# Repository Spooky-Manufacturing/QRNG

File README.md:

# QRNG
Quantum Random Number Generator

# Motivation
The QRNGv1 (Now QRNG_BASIC) was originally a proof of concept for quantum technology applications, specifically in this case for the generation of entropy which has a broad range of uses from generating graphics to encryption keys.

# How It Works
The device uses a polarizing beam splitter to split a laser pulse into two beams with a 50/50 probability of a photon in the beam traveling either path. The photons actually travel as a wave, meaning they both pass through and are reflected by the beam splitter. This creates what's known as the superposition of light where the light remains in both paths able to interfere with itself until it is measured and collapses out of superposition.

The equivalent quantum logic gate would be the Hadamard gate, in QASM code:

```qasm
creg c0[1];
h q[1];
measure q[1] -> c0;
```

# Hardware Requirements
- Arduino Uno (or similar)
- Breadboard
- 2x Photoresistors
- 1x 50/50 Polarizing beam splitter
- 1x Laser Diode

# Software Requirements
- Arduino IDE (for programming the Arduino)

# Firmware
Firmware can be found in the respective design folders labelled according to version. The schematics as well are labelled with the version of firmware which supports them.

# How To Use
Currently the QRNG arduino operates via the Arduino Serial Monitor, you can issue single letter commands to it. We plan to add support for the device with our [Qubit Controller](https://github.com/Spooky-Manufacturing/Qubit-Controller) in the near future.

## Available Commands
- v : Version, returns the current firmware verison
- t : Test command, should return 'Success!' on the monitor
- e : Enables extraneous information
- r : Returns a random bit generated by the RNG
- h : Produces a hadamard operation on the qubit, returning the measured angle of the qubit

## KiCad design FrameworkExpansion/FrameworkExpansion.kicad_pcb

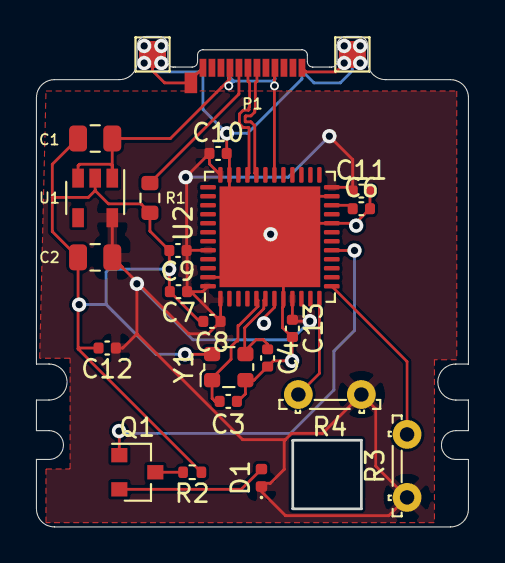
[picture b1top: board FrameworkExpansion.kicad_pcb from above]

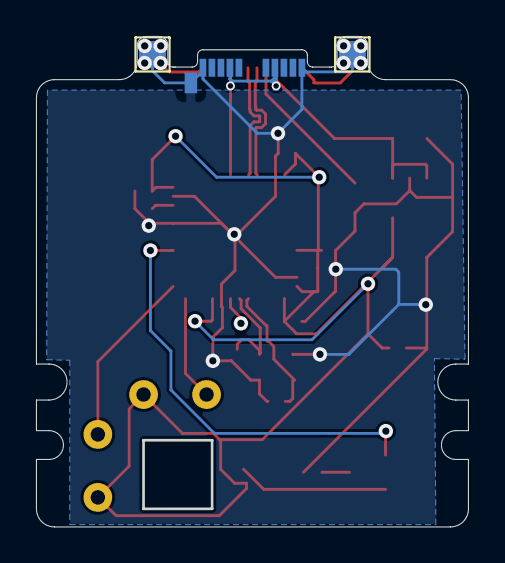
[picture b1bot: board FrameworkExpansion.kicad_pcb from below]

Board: 2 copper layers, 23.9 x 27.2 mm, 26 parts (2 on the bottom side), 14 nets.

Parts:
C1, C2: 10uF; C_0805_2012Metric
C3, C4: C_Small; C_0402_1005Metric
C6: 4.7uF; C_0402_1005Metric
C7, C8, C9, C10, C11, C12, C13: 100nF; C_0402_1005Metric
D1: LED; LED_0402_1005Metric
P1: USB_C_Plug_USB2.0; USB_C_Plug_Molex_105444
Q1: Q_NPN_BCE; SOT-23
R1: 5.1k; R_0603_1608Metric
R2: 10k; R_0402_1005Metric
R3, R4: R_PHOTO; R_LDR_5.2x5.2mm_P3.5mm_Horizontal
TP1, TP2, TP3, TP4: TestPoint; TestPoint_Pad_1.5x1.5mm
U1: AP2112K-3.3; SOT-23-5
U2: STM32F411CEUx; QFN-48-1EP_7x7mm_P0.5mm_EP5.6x5.6mm
Y1: Crystal_GND24; Oscillator_SMD_ECS_2520MV-xxx-xx-4Pin_2.5x2.0mm

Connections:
+3V3: C2.1, C7.1, C8.1, C9.1, C10.1, C11.1, C12.1, C13.1, D1.1, R3.1, R4.1, U1.5, U2.1, U2.9, U2.24, U2.36, U2.44, U2.48
/HORIZONTAL: R4.2, U2.12
/TRIGGER: Q1.1, U2.17
/USB_DN: P1.A7, U2.32
/USB_DP: P1.A6, U2.33
/VERTICAL: R3.2, U2.13
/XTAL_N: C4.1, U2.6, Y1.3
/XTAL_P: C3.1, U2.5, Y1.1
GND: C1.2, C2.2, C3.2, C4.2, C6.2, C7.2, C8.2, C9.2, C10.2, C11.2, C12.2, C13.2, P1.A1, P1.A12, P1.B1, P1.B12, P1.S1, R1.2, R2.1, TP1.1, TP2.1, TP3.1, TP4.1, U1.2, U2.8, U2.20, U2.23, U2.35, U2.47, U2.49, Y1.2, Y1.4
unnamed: C6.1, U2.22
unnamed: D1.2, Q1.2
unnamed: P1.A5, R1.1
unnamed: Q1.3, R2.2
VBUS: C1.1, P1.A4, P1.A9, P1.B4, P1.B9, U1.1, U1.3, U2.30

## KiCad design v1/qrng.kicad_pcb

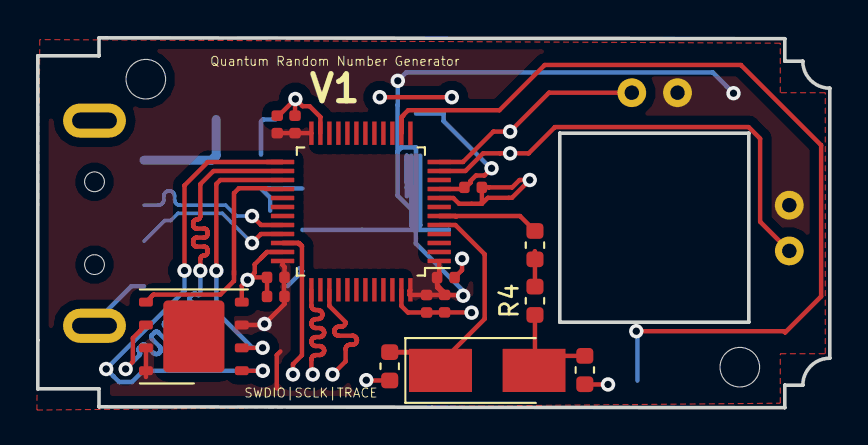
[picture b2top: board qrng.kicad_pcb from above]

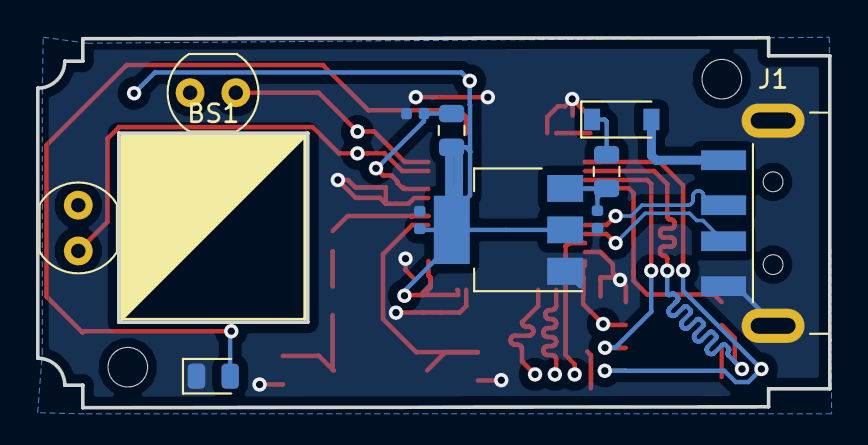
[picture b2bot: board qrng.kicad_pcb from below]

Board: 2 copper layers, 44.0 x 20.5 mm, 29 parts (12 on the bottom side), 19 nets.

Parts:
BS1: Macro-Beam-Splitter
C1: 4.7uF; C_0402_1005Metric
C2, C3, C4, C5, C6, C7, C10: 100nF; C_0402_1005Metric
C8, C9: 10uF; C_0402_1005Metric
C11: 10nF; C_0402_1005Metric
C12, C13: 30pF; C_0603_1608Metric
D1: B5819W; D_SOD-123
D2: LED; LED_0805_2012Metric
FB1, FB2: 100ohm @ 100mHz; L_0805_2012Metric
H1, H2: MountingHole; MountingHole_2.2mm_M2
J1: USB_A; USB_A_CNCTech_1001-011-01101_Horizontal
R2, R3: R_PHOTO; R_LDR_4.9x4.2mm_P2.54mm_Vertical
R4: 270; R_0603_1608Metric
R5: 100; R_0603_1608Metric
U1: AMS1117; SOT-223-3_TabPin2
U2: STM32F103C8Tx; LQFP-48_7x7mm_P0.5mm
U3: W25N01GV; WSON-8-1EP_6x5mm_P1.27mm_EP3.4x4mm
Y1: 8 MHz; Crystal_SMD_5032-2Pin_5.0x3.2mm_HandSoldering

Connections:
+3.3VA: C10.1, C11.1, FB2.1, U2.9
+3V3: C1.1, C2.1, C3.1, C4.1, C5.1, C6.1, C7.1, C9.1, FB2.2, R2.2, R3.1, U1.2, U2.1, U2.24, U2.36, U2.48, U3.3, U3.7, U3.8
+5V: D1.2, J1.1
ADC1: R3.2, U2.11
ADC2: R2.1, U2.12
GND: C1.2, C2.2, C3.2, C4.2, C5.2, C6.2, C7.2, C8.2, C9.2, C10.2, C11.2, C12.1, C13.1, D2.1, J1.4, J1.5, U1.1, U2.8, U2.23, U2.35, U2.47, U3.4
MEM_MISO: U2.27, U3.2
MEM_MOSI: U2.28, U3.5
MEM_NSS: U2.25, U3.1
MEM_SCK: U2.26, U3.6
unnamed: C8.1, FB1.1, U1.3
unnamed: C13.2, R4.1, Y1.2
unnamed: D1.1, FB1.2
unnamed: R4.2, R5.1
OSC_IN: C12.2, U2.5, Y1.1
OSC_OUT: R5.2, U2.6
USB_D+: J1.3, U2.33
USB_D-: J1.2, U2.32
trigger: D2.2, U2.14

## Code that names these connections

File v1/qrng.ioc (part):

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Mcu.Name=STM32F103C(8-B)Tx
Mcu.Package=LQFP48
Mcu.UserName=STM32F103CBTx
PA1.Signal=ADCx_IN1
PA11.Mode=Device
PA11.Signal=USB_DM
PA12.Mode=Device
PA12.Signal=USB_DP
PA13.Mode=Trace_Asynchronous_SW
PA13.Signal=SYS_JTMS-SWDIO
PA14.Mode=Trace_Asynchronous_SW
PA14.Signal=SYS_JTCK-SWCLK
PA2.Signal=ADCx_IN2
PA4.Signal=GPIO_Output
PB12.Mode=NSS_Signal_Hard_Output
PB12.Signal=SPI2_NSS
PB13.Mode=Full_Duplex_Master
PB13.Signal=SPI2_SCK
PB14.Mode=Full_Duplex_Master
PB14.Signal=SPI2_MISO
PB15.Mode=Full_Duplex_Master
PB15.Signal=SPI2_MOSI
PB3.Mode=Trace_Asynchronous_SW
PB3.Signal=SYS_JTDO-TRACESWO
PD0-OSC_IN.Mode=HSE-External-Clock-Source
PD0-OSC_IN.Signal=RCC_OSC_IN
PD1-OSC_OUT.Mode=HSE-External-Clock-Source
PD1-OSC_OUT.Signal=RCC_OSC_OUT
RCC.SYSCLKFreq_VALUE=48000000
RCC.SYSCLKSource=RCC_SYSCLKSOURCE_PLLCLK
board=custom

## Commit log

2019-10-11 Created QRNGv1
2020-05-15 Renamed v1 to "BASIC" Created a new v1 design which integrates USB, microcontroller, and storage Updated readme Add PCB layout, gerber, and assembly files
2020-07-31 Separated ADC pins per recommendation from Epilogis
2021-11-21 new file: FrameworkExpansion/Expansion_Card.pretty/Framework-Logo_1.5mm_SilkScreen.kicad_mod new file: FrameworkExpansion/Expansion_Card.pretty/PinSocket_8FM-78-0010-02-146_1x10_P2.54mm_Horizontal_SM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
2022-04-28 Correcting "Firmare" to "Firmware"
    Just a simple spelling mistake :)

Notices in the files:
FrameworkExpansion/FrameworkExpansion.kicad_pcb:
This work is licensed under a Creative Commons Attribution 4.0 International License
v1/qrng.kicad_pcb:
(c) 2020
